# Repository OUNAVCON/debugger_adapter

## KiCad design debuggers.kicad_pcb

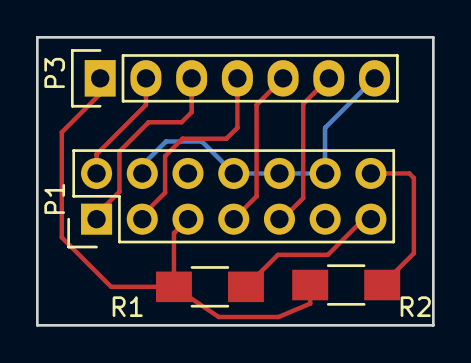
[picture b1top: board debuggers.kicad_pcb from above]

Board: 2 copper layers, 22.0 x 16.0 mm, 4 parts (0 on the bottom side), 9 nets.

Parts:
P1: TI_JTAG; Pin_Header_Straight_2x07
P3: TI_jtag; Pin_Header_Straight_1x07
R1, R2: 4k7; R_1206_HandSoldering

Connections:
/3v3: P1.5, P3.1, R1.2, R2.2
/TCK: P1.9, P3.6
/TDI: P1.3, P3.4
/TDO: P1.7, P3.5
/TI_GND: P1.4, P1.8, P1.10, P1.12, P3.7
/TMS: P1.1, P3.3
/Trst: P1.2, P3.2
unnamed: P1.13, R1.1
unnamed: P1.14, R2.1

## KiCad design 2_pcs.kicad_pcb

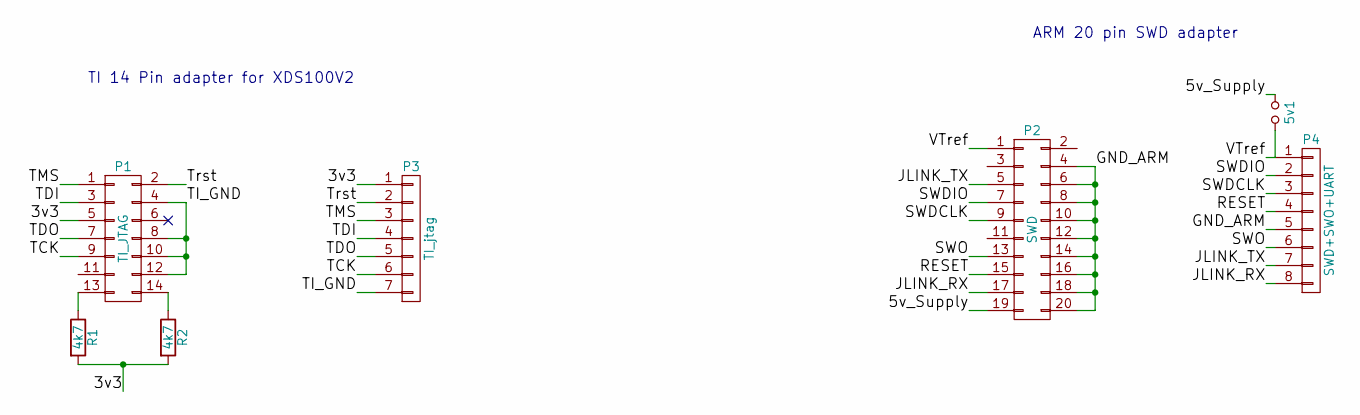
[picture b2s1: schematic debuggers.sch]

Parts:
5v1: Jumper_NO_Small; Pin_Header_Straight_1x02_Pitch2.54mm
P1: TI_JTAG; Pin_Header_Straight_1x02_Pitch2.00mm
P2: SWD; Pin_Header_Straight_2x10_Pitch2.54mm
P3: TI_jtag; Pin_Header_Straight_1x29_Pitch2.00mm_SMD_Pin1Right
P4: SWD+SWO+UART; Pin_Header_Straight_1x08_Pitch2.54mm
R1, R2: 4k7; Relay_SPDT_PotterBrumfield_T9AP5D52_12V30A

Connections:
/3v3: P1.5, P3.1, R1.2, R2.2
/5v_Supply: 5v1.1, P2.19
/GND_ARM: P2.4, P2.6, P2.8, P2.10, P2.12, P2.14, P2.16, P2.18, P2.20, P4.5
/JLINK_RX: P2.17, P4.8
/JLINK_TX: P2.5, P4.7
/RESET: P2.15, P4.4
/SWDCLK: P2.9, P4.3
/SWDIO: P2.7, P4.2
/SWO: P2.13, P4.6
/TCK: P1.9, P3.6
/TDI: P1.3, P3.4
/TDO: P1.7, P3.5
/TI_GND: P1.4, P1.8, P1.10, P1.12, P3.7
/TMS: P1.1, P3.3
/Trst: P1.2, P3.2
/VTref: 5v1.2, P2.1, P4.1
unnamed: P1.13, R1.1
unnamed: P1.14, R2.1

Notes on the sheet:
TI 14 Pin adapter for XDS100V2
ARM 20 pin SWD adapter

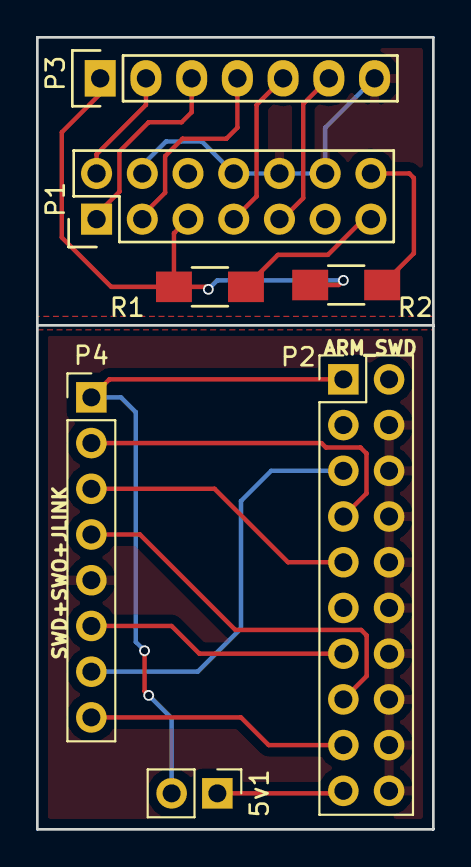
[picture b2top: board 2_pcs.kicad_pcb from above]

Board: 2 copper layers, 22.0 x 44.0 mm, 7 parts (0 on the bottom side), 18 nets.

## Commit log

2018-03-02 Updated files for production
2018-03-15 Added schematics
2018-03-16 Created Seperate boards for each debugger
2018-03-16 Created Seperate boards for each debugger...Missed the files last time.
2018-03-19 Updated layouts
